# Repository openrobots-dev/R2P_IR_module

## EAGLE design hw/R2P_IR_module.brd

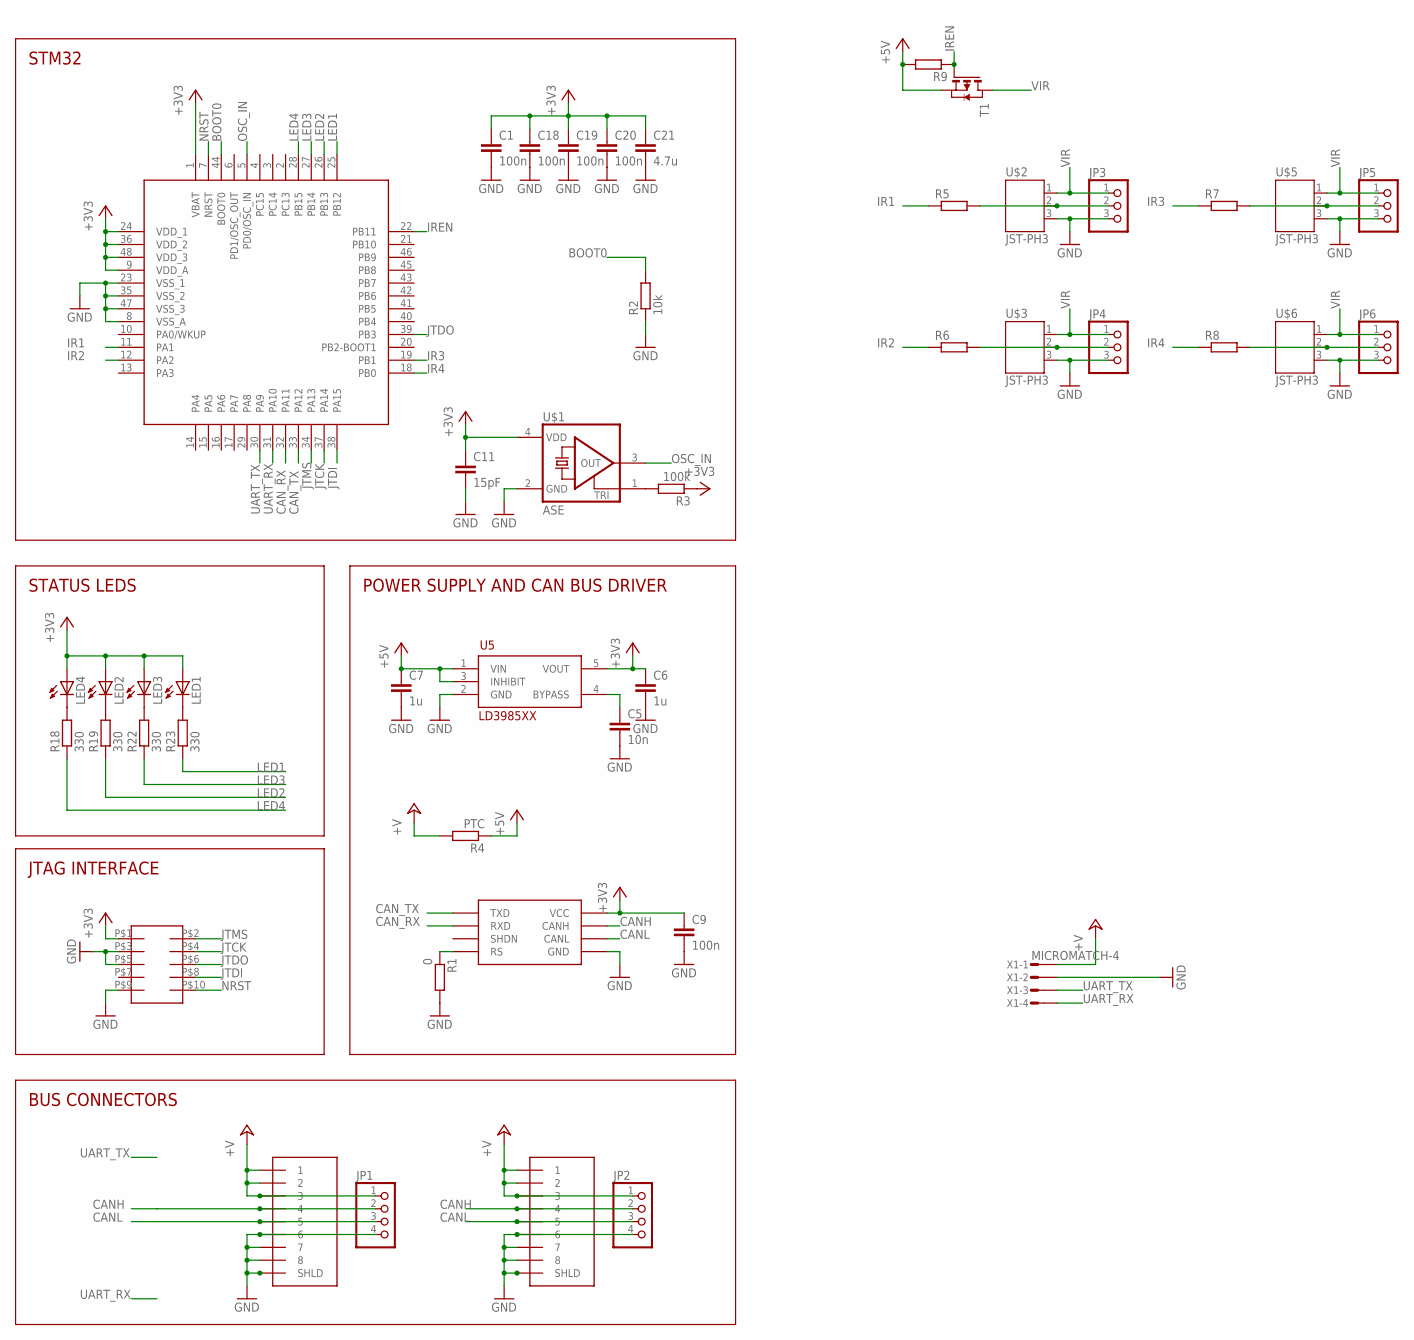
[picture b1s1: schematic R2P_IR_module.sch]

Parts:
1, 2: RJ45-43860; 0438600010
C1, C9, C18, C19, C20: 100n; C0603
C5: 10n; C0603
C6, C7: 1u; C0603
C11: 15pF; C0603
C21: 4.7u; C0805
JP1, JP2: PINHD-1X4; 1X04
JP3, JP4, JP5, JP6: PINHD-1X3; 1X03
LED1, LED2, LED3, LED4: LEDCHIPLED_0805; CHIPLED_0805
R1: 0; R0603
R2: 10k; R0603
R3: 100k; R0603
R4: PTC; R0603
R5, R6, R7, R8, R9: R-EU_R0603; R0603
R18, R19, R22, R23: 330; R0603
SOT1: MAX3051; SOT23-8L
T1: PMOSSOT23; SOT-23
U1: STM32F103CX; LQFP48
U5: LD3985XX; SOT23-5L
U$1: ASE
U$2, U$3, U$5, U$6: JST-PH3
U$4: FTSH-105
X1: MICROMATCH-4

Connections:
+3V3: C1.1, C6.1, C9.1, C11.1, C18.1, C19.1, C20.1, C21.1, LED1.A, LED2.A, LED3.A, LED4.A, R3.1, SOT1.P$3 (VCC), U1.1 (VBAT), U1.9 (VDD_A), U1.24 (VDD_1), U1.36 (VDD_2), U1.48 (VDD_3), U5.5 (VOUT), U$1.4 (VDD), U$4.P$1
+5V: C7.1, R4.1, R9.2, T1.2 (S), U5.1 (VIN), U5.3 (INHIBIT)
+V: 1.P$1 (1), 1.P$2 (2), 1.P$3 (3), 2.P$1 (1), 2.P$2 (2), 2.P$3 (3), JP1.1, JP2.1, R4.2, X1.1
BOOT0: R2.2, U1.44 (BOOT0)
CANH: 1.P$4 (4), 2.P$4 (4), JP1.2, JP2.2, SOT1.P$7 (CANH)
CANL: 1.P$5 (5), 2.P$5 (5), JP1.3, JP2.3, SOT1.P$6 (CANL)
CAN_RX: SOT1.P$4 (RXD), U1.32 (PA11)
CAN_TX: SOT1.P$1 (TXD), U1.33 (PA12)
GND: 1.P$6 (6), 1.P$7 (7), 1.P$8 (8), 1.P$9 (SHLD), 1.P$10, 2.P$6 (6), 2.P$7 (7), 2.P$8 (8), 2.P$9 (SHLD), 2.P$10, C1.2, C5.2, C6.2, C7.2, C9.2, C11.2, C18.2, C19.2, C20.2, C21.2, JP1.4, JP2.4, JP3.3, JP4.3, JP5.3, JP6.3, R1.2, R2.1, SOT1.P$2 (GND), U1.8 (VSS_A), U1.23 (VSS_1), U1.35 (VSS_2), U1.47 (VSS_3), U5.2 (GND), U$1.2 (GND), U$2.3, U$3.3, U$4.P$3, U$4.P$5, U$4.P$9, U$5.3, U$6.3, X1.2
IR1: R5.1, U1.11 (PA1)
IR2: R6.1, U1.12 (PA2)
IR3: R7.1, U1.19 (PB1)
IR4: R8.1, U1.18 (PB0)
IREN: R9.1, T1.3 (G), U1.22 (PB11)
JTCK: U1.37 (PA14), U$4.P$4
JTDI: U1.38 (PA15), U$4.P$8
JTDO: U1.39 (PB3), U$4.P$6
JTMS: U1.34 (PA13), U$4.P$2
LED1: R23.1, U1.25 (PB12)
LED2: R19.1, U1.26 (PB13)
LED3: R22.1, U1.27 (PB14)
LED4: R18.1, U1.28 (PB15)
unnamed: R1.1, SOT1.P$8 (RS)
unnamed: R3.2, U$1.1 (TRI)
unnamed: C5.1, U5.4 (BYPASS)
unnamed: JP3.2, R5.2, U$2.2
unnamed: JP4.2, R6.2, U$3.2
unnamed: JP6.2, R8.2, U$6.2
unnamed: JP5.2, R7.2, U$5.2
unnamed: LED4.C, R18.2
unnamed: LED2.C, R19.2
unnamed: LED3.C, R22.2
unnamed: LED1.C, R23.2
NRST: U1.7 (NRST), U$4.P$10
OSC_IN: U1.5 (PD0/OSC_IN), U$1.3 (OUT)
UART_RX: U1.31 (PA10), X1.4
UART_TX: U1.30 (PA9), X1.3
VIR: JP3.1, JP4.1, JP5.1, JP6.1, T1.1 (D), U$2.1, U$3.1, U$5.1, U$6.1

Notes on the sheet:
STM32
POWER SUPPLY AND CAN BUS DRIVER
STATUS LEDS
JTAG INTERFACE
BUS CONNECTORS

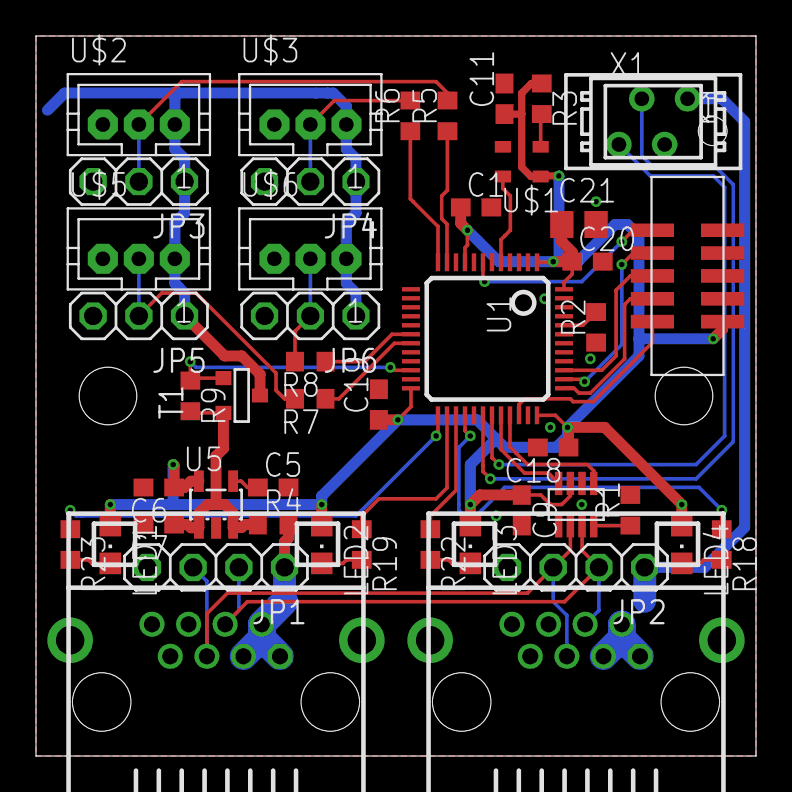
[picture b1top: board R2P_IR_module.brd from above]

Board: 2 copper layers, 40.0 x 40.0 mm, 46 parts (0 on the bottom side), 38 nets.

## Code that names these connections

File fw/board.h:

/*
 ChibiOS/RT - Copyright (C) 2006,2007,2008,2009,2010,
 2011 Giovanni Di Sirio.

 This file is part of ChibiOS/RT.

 ChibiOS/RT is free software; you can redistribute it and/or modify
 it under the terms of the GNU General Public License as published by
 the Free Software Foundation; either version 3 of the License, or
 (at your option) any later version.

 ChibiOS/RT is distributed in the hope that it will be useful,
 but WITHOUT ANY WARRANTY; without even the implied warranty of
 MERCHANTABILITY or FITNESS FOR A PARTICULAR PURPOSE.  See the
 GNU General Public License for more details.

 You should have received a copy of the GNU General Public License
 along with this program.  If not, see <http://www.gnu.org/licenses/>.
 */

#ifndef _BOARD_H_
#define _BOARD_H_

/*
 * Setup for the R2P Sonar module.
 */

/*
 * Board identifier.
 */
#define BOARD_R2P_IR_MODULE
#define BOARD_NAME              "R2P IR module"

/*
 * Board frequencies.
 */
#define STM32_LSECLK            32768
#define STM32_HSECLK            8000000

/*
 * MCU type, supported types are defined in ./os/hal/platforms/hal_lld.h.
 */
#define STM32F10X_MD

/*
 * IO pins assignments.
 */
#define LED_GPIO				GPIOB
#define LED1_GPIO				GPIOB
#define LED1					12
#define LED2_GPIO				GPIOB
#define LED2					13
#define LED3_GPIO				GPIOB
#define LED3					14
#define LED4_GPIO				GPIOB
#define LED4					15

#define IREN_GPIO				GPIOB
#define IREN					11

#define SERIAL_DRIVER           SD1
#define ADC_DRIVER              ADCD1
#define ICU_DRIVER              ICUD2

/*
 * I/O ports initial setup, this configuration is established soon after reset
 * in the initialization code.
 *
 * The digits have the following meaning:
 *   0 - Analog input.
 *   1 - Push Pull output 10MHz.
 *   2 - Push Pull output 2MHz.
 *   3 - Push Pull output 50MHz.
 *   4 - Digital input.
 *   5 - Open Drain output 10MHz.
 *   6 - Open Drain output 2MHz.
 *   7 - Open Drain output 50MHz.
 *   8 - Digital input with PullUp or PullDown resistor depending on ODR.
 *   9 - Alternate Push Pull output 10MHz.
 *   A - Alternate Push Pull output 2MHz.
 *   B - Alternate Push Pull output 50MHz.
 *   C - Reserved.
 *   D - Alternate Open Drain output 10MHz.
 *   E - Alternate Open Drain output 2MHz.
 *   F - Alternate Open Drain output 50MHz.
 * Please refer to the STM32 Reference Manual for details.
 */

/*
 * Port A setup.
 * Everything input with pull-up except:
 * PA1  - Analog input     (IR1).
 * PA2  - Analog input     (IR2).
 * PA9  - Alternate output (USART1 TX).
 * PA10 - Normal input     (USART1 RX).
 * PA11 - Normal input     (CAN1 RX).
 * PA12 - Alternate output (CAN1 TX).
 */
#define VAL_GPIOACRL            0x88888008      /*  PA7...PA0 */
#define VAL_GPIOACRH            0x888B44B8      /* PA15...PA8 */
#define VAL_GPIOAODR            0xFFFFFFFF

/*
 * Port B setup.
 * Everything input with pull-up except:
 *
 * PB0  - Analog input     (IR3).
 * PB1  - Analog input     (IR4).
 * PB11 - Open Drain output (IREN).
 * PB12 - Push Pull output (LED1).
 * PB13 - Push Pull output (LED2).
 * PB14 - Push Pull output (LED3).
 * PB15 - Push Pull output (LED4).
 */
#define VAL_GPIOBCRL            0x88888800      /*  PB7...PB0 */
#define VAL_GPIOBCRH            0x33337888      /* PB15...PB8 */
#define VAL_GPIOBODR            0xFFFFFFFF

/*
 * Port C setup.
 * Everything input with pull-up except:
 */
#define VAL_GPIOCCRL            0x88888888      /*  PC7...PC0 */
#define VAL_GPIOCCRH            0x88888888      /* PC15...PC8 */
#define VAL_GPIOCODR            0xFFFFFFFF

#if !defined(_FROM_ASM_)
#ifdef __cplusplus
extern "C" {
#endif
void boardInit(void);
#ifdef __cplusplus
}
#endif
#endif /* _FROM_ASM_ */

#endif /* _BOARD_H_ */

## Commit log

2012-07-31 Added .gitignore
2012-07-31 Ongoing board layout
2012-08-01 Board layout complete
2012-08-01 Added PMOS to shut down IR sensors
2013-07-05 Test firmware
2014-07-08 demo setup
